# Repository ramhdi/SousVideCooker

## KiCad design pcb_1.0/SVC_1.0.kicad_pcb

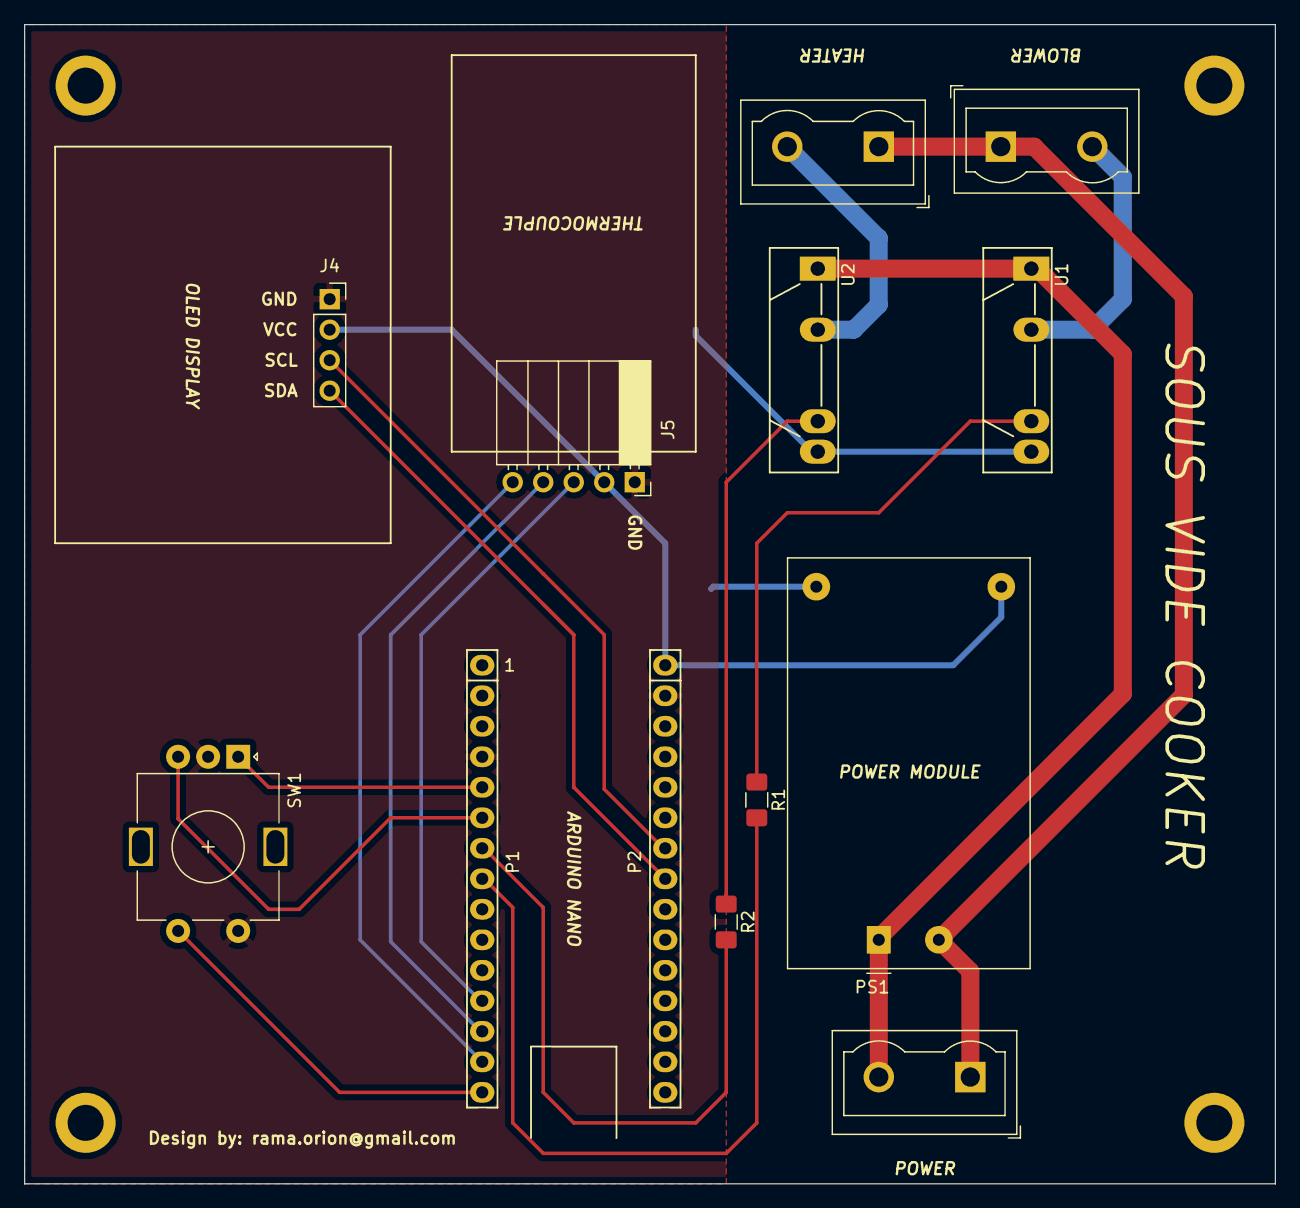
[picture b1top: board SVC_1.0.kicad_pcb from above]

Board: 2 copper layers, 104.1 x 96.5 mm, 13 parts (0 on the bottom side), 19 nets.

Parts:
J1, J2, J3: Screw_Terminal_01x02; TerminalBlock_Wuerth_691311400102_P7.62mm
J4: Conn_01x04; PinSocket_1x04_P2.54mm_Vertical
J5: Conn_01x05; PinSocket_1x05_P2.54mm_Horizontal
P1: Digital; Socket_Strip_Arduino_1x15
P2: Analog; Socket_Strip_Arduino_1x15
PS1: HLK-PM01; Converter_ACDC_HiLink_HLK-PMxx
R1, R2: R; R_1206_3216Metric_Pad1.42x1.75mm_HandSolder
SW1: Rotary_Encoder_Switch; RotaryEncoder_Alps_EC11E-Switch_Vertical_H20mm
U1, U2: S202S01; SIP4_Sharp-SSR_P7.62mm_Straight

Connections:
+5V: J4.2, J5.2, P2.1, PS1.4
/Reset: P1.3, P2.3
AC+: J1.2, PS1.1, U1.1, U2.1
AC-: J1.1, J2.1, J3.1, PS1.2
BLOWER_CTRL: P1.7, R2.2
BLOWER_OUT: J3.2, U2.2
CS: J5.4, P1.13
GND: J4.1, J5.1, P1.4, P2.2, PS1.3, SW1.C, SW1.S2, U1.4, U2.4
HEATER_CTRL: P1.8, R1.2
HEATER_OUT: J2.2, U1.2
unnamed: R1.1, U1.3
unnamed: R2.1, U2.3
RE_A: P1.5, SW1.A
RE_B: P1.6, SW1.B
RE_SW: P1.15, SW1.S1
SCK: J5.3, P1.12
SCL: J4.3, P2.7
SDA: J4.4, P2.8
SO: J5.5, P1.14
